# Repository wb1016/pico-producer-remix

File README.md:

# ARCHIVED
### will be on work for new fork
# Pico Producer remix by Blue_ON

a shorcut keypad using YD-RP2040/Pi Pico.\
original project by https://github.com/pjgpetecodes/pico-streamdeck

# Parts List
all parts are THT components, making easy to assemble.

| Part | Qty | note |
|------|-----|------|
| PCB | 1 | generate with kicad |
| 3mm THT LED | 12 |  |
| Cherry MX switches | 12 | compatible switches can be used | 
| 1k Ohm THT Resistor | 12 |  |
| YD-RP2040 | 1 | you can use Pi Pico instead |
| 20 pin Header pin | 2 | will come with YD-RP2040 |
| 3D Printed Case | 1 |  |
| 3D printed keycaps | 12 |  |
| 3D printed faceplate | 1 |  |

Notes: 
- you can use Pi Pico instead, but you will need external WS2812B LED.
- print 3D models with 25% infill at least.

# Instructions
- connect YD-RP2040 to computer while pressing onboard BOOT button.
- download circuitpython for YD-RP2040 [link](https://circuitpython.org/board/vcc_gnd_yd_rp2040/)
- install circuitpython to YD-RP2040 by copying uf2 file to newly appeared drive.
- install [neopixel driver](https://github.com/adafruit/Adafruit_CircuitPython_NeoPixel/releases) to 'CIRCUITPY' drive
- install [hid library](https://github.com/adafruit/Adafruit_CircuitPython_HID/releases) to 'CIRCUITPY' drive
- copy code.py to 'CIRCUITPY' drive and disconnect the board from computer.
- solder the R68 jumper on the YD-RP2040. this enables onboard RGB LED.
- solder LEDs to PCB.
- solder resistors to PCB.
- solder pin header to PCB.
- solder key switches to PCB.
- solder YD-RP2040 to PCB.
- trim the header pins.
- assemble all together.

## CircuitPython HID

You can find some more info about the CircuitPython KeyMappings here;

https://circuitpython.readthedocs.io/projects/hid/en/latest/_modules/adafruit_hid/keycode.html

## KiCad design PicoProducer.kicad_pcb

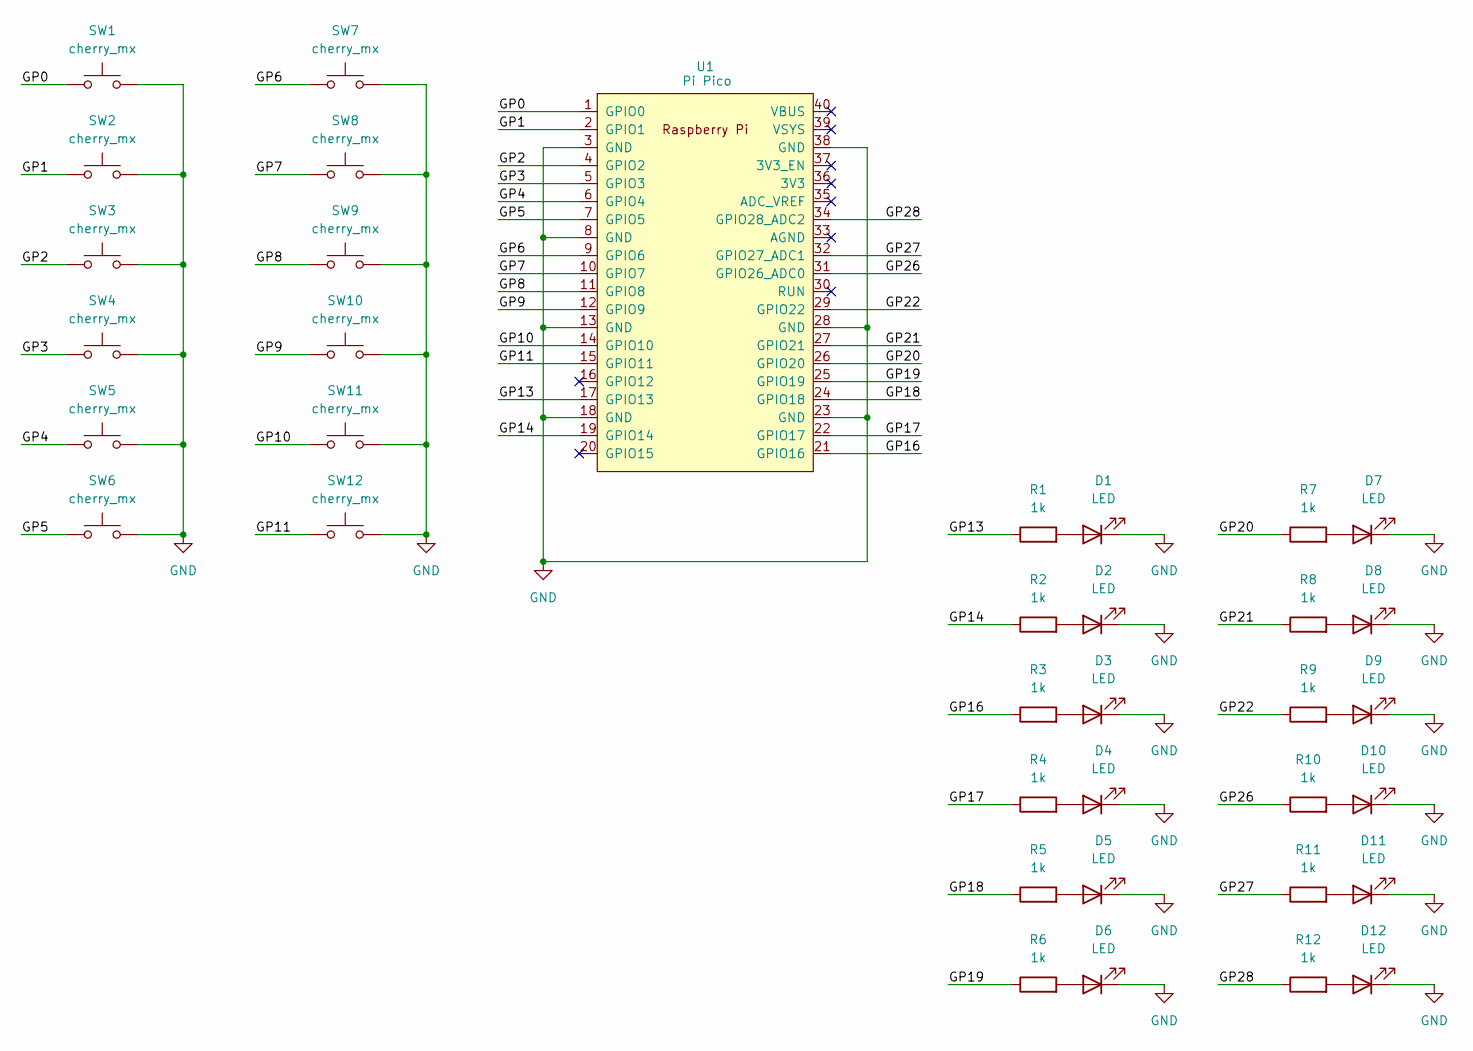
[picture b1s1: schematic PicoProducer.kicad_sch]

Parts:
D1, D2, D3, D4, D5, D6, D7, D8, D9, D10, D11, D12: LED; LED_0805_2012Metric_Pad1.15x1.40mm_HandSolder
R1, R2, R3, R4, R5, R6, R7, R8, R9, R10, R11, R12: 1k; R_0805_2012Metric_Pad1.20x1.40mm_HandSolder
SW1, SW2, SW3, SW4, SW5, SW6, SW7, SW8, SW9, SW10, SW11, SW12: cherry_mx; SW_Cherry_MX_1.00u_PCB
U1: Pi Pico; YD-RP2040

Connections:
/GP0: SW1.1, U1.1 (GPIO0)
/GP1: SW2.1, U1.2 (GPIO1)
/GP2: SW3.1, U1.4 (GPIO2)
/GP3: SW4.1, U1.5 (GPIO3)
/GP4: SW5.1, U1.6 (GPIO4)
/GP5: SW6.1, U1.7 (GPIO5)
/GP6: SW7.1, U1.9 (GPIO6)
/GP7: SW8.1, U1.10 (GPIO7)
/GP8: SW9.1, U1.11 (GPIO8)
/GP9: SW10.1, U1.12 (GPIO9)
/GP10: SW11.1, U1.14 (GPIO10)
/GP11: SW12.1, U1.15 (GPIO11)
/GP13: R1.1, U1.17 (GPIO13)
/GP14: R2.1, U1.19 (GPIO14)
/GP16: R3.1, U1.21 (GPIO16)
/GP17: R4.1, U1.22 (GPIO17)
/GP18: R5.1, U1.24 (GPIO18)
/GP19: R6.1, U1.25 (GPIO19)
/GP20: R7.1, U1.26 (GPIO20)
/GP21: R8.1, U1.27 (GPIO21)
/GP22: R9.1, U1.29 (GPIO22)
/GP26: R10.1, U1.31 (GPIO26_ADC0)
/GP27: R11.1, U1.32 (GPIO27_ADC1)
/GP28: R12.1, U1.34 (GPIO28_ADC2)
GND: D1.1 (K), D2.1 (K), D3.1 (K), D4.1 (K), D5.1 (K), D6.1 (K), D7.1 (K), D8.1 (K), D9.1 (K), D10.1 (K), D11.1 (K), D12.1 (K), SW1.2, SW2.2, SW3.2, SW4.2, SW5.2, SW6.2, SW7.2, SW8.2, SW9.2, SW10.2, SW11.2, SW12.2, U1.3 (GND), U1.8 (GND), U1.13 (GND), U1.18 (GND), U1.23 (GND), U1.28 (GND), U1.38 (GND)
unnamed: D1.2 (A), R1.2
unnamed: D2.2 (A), R2.2
unnamed: D3.2 (A), R3.2
unnamed: D4.2 (A), R4.2
unnamed: D5.2 (A), R5.2
unnamed: D6.2 (A), R6.2
unnamed: D7.2 (A), R7.2
unnamed: D8.2 (A), R8.2
unnamed: D9.2 (A), R9.2
unnamed: D10.2 (A), R10.2
unnamed: D11.2 (A), R11.2
unnamed: D12.2 (A), R12.2

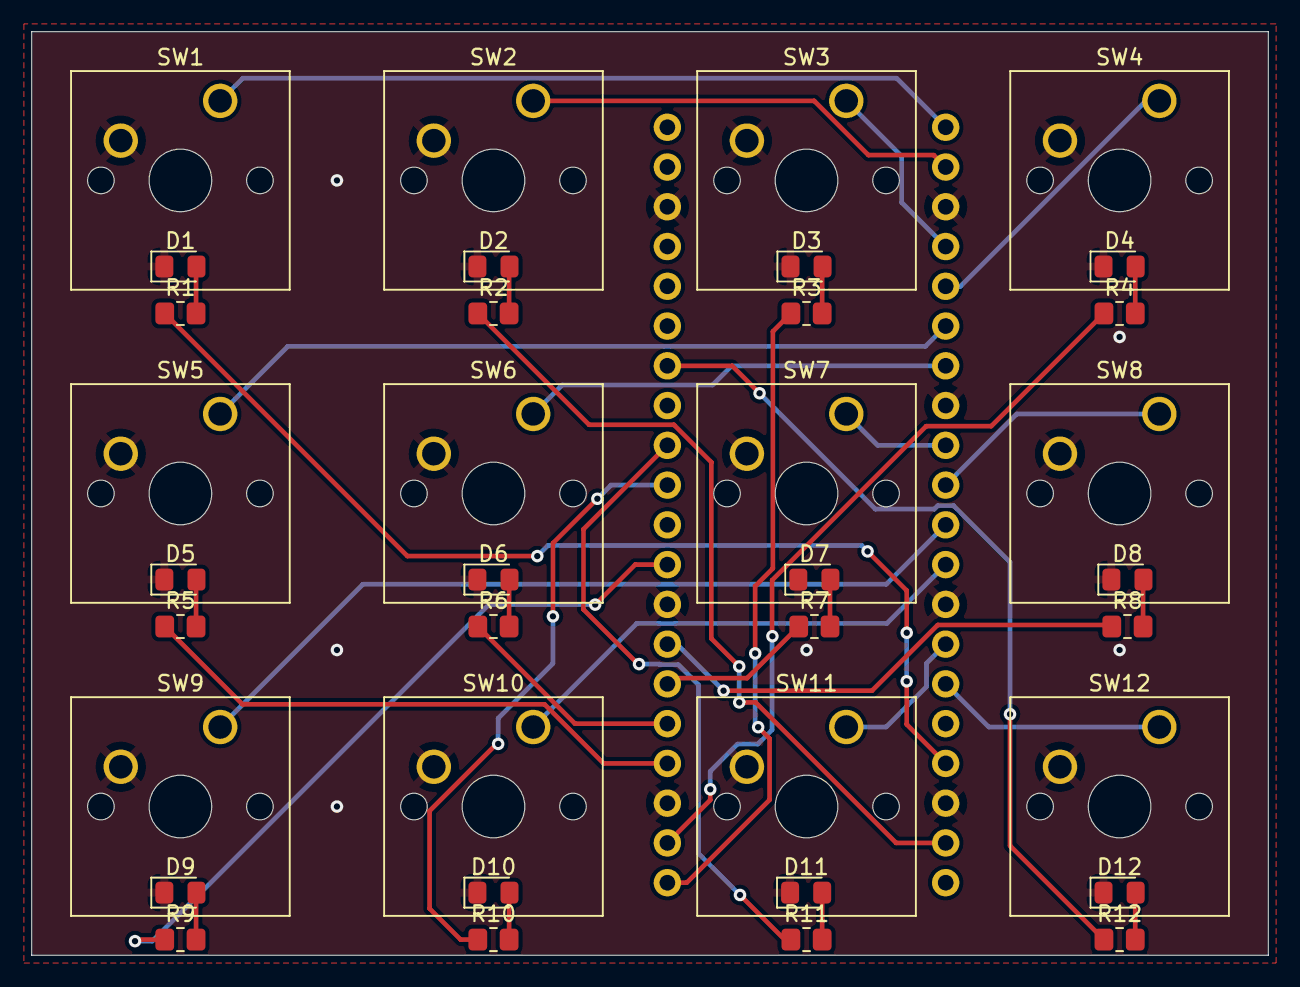
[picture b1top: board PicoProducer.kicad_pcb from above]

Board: 2 copper layers, 79.0 x 59.0 mm, 37 parts (1 on the bottom side), 37 nets.

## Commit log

2024-03-06 ඞreadmeඞ
2024-03-10 reorder readme, enlarge usb port hole in case stl
2024-03-20 3dmodels
2024-03-22 case hight adjustment
2024-03-22 thicken faceplate
2024-03-22 maybe that was too thicc
2024-05-10 gitignore
2024-09-21 resolve drc errors
2024-10-09 3dfiles
2024-10-13 3dmodel
2024-11-09 3dfiles update
2024-11-09 refine 3dfiles
